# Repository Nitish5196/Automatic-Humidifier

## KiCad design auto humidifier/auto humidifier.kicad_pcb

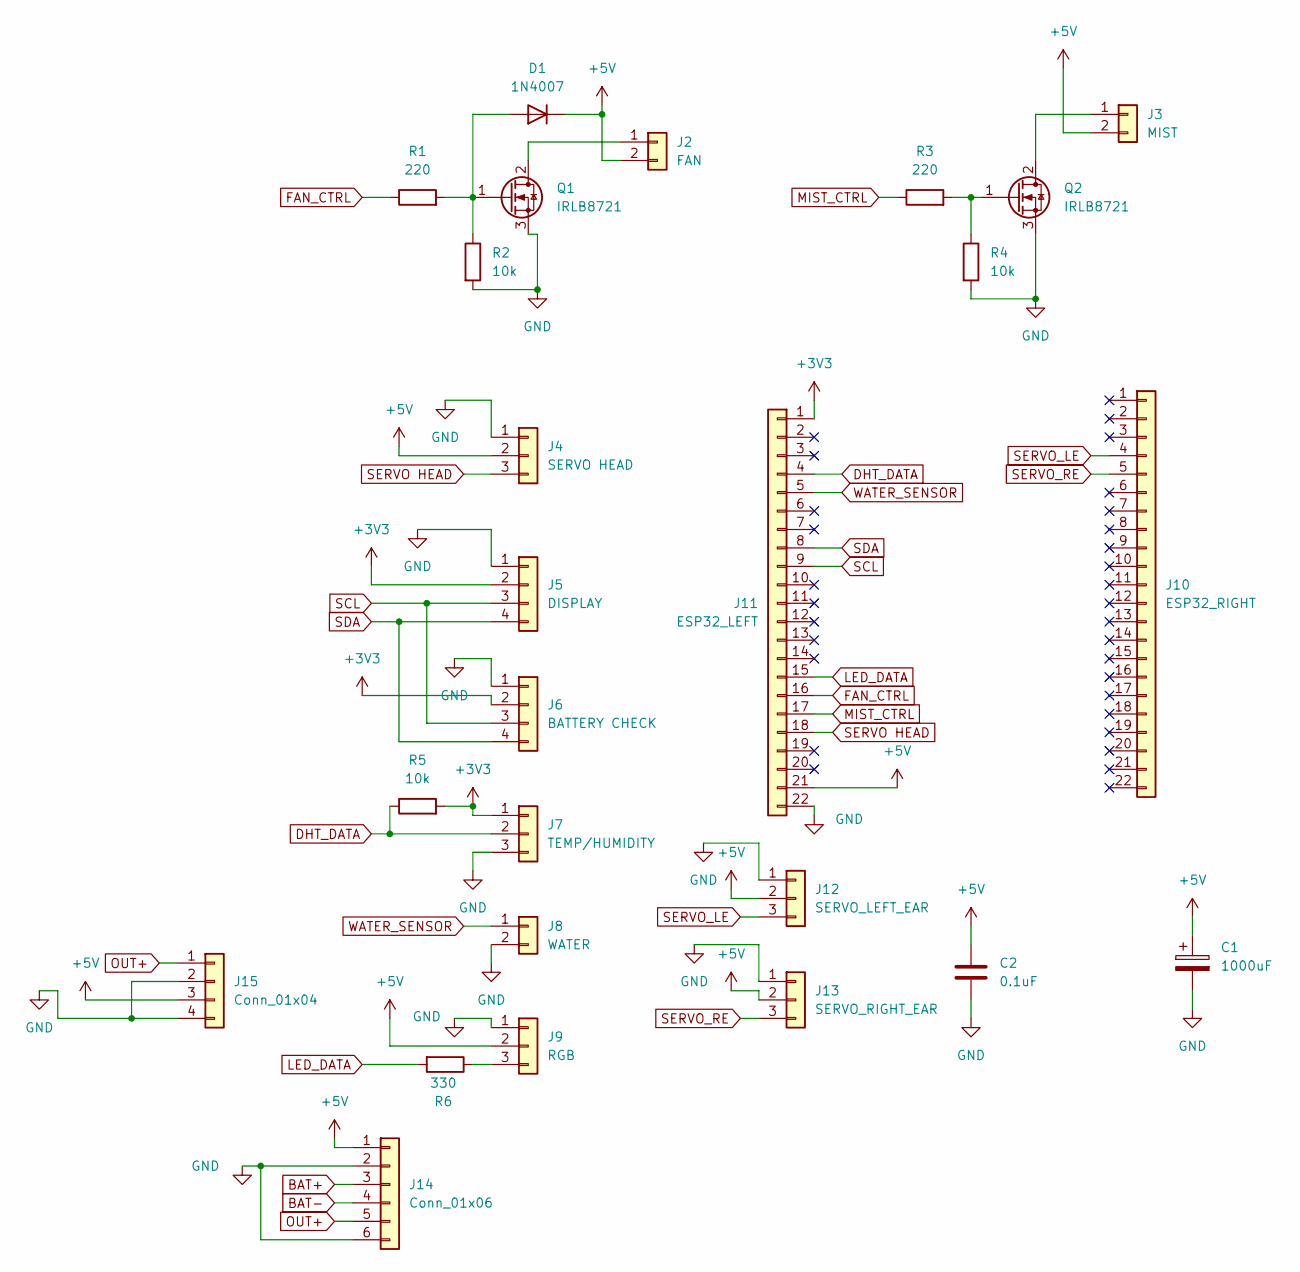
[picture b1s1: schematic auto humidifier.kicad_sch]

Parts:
C1: 1000uF; CP_Radial_D10.0mm_P5.00mm
C2: 0.1uF; C_0805_2012Metric
D1: 1N4007; D_DO-41_SOD81_P10.16mm_Horizontal
J2: FAN; PinHeader_1x02_P2.54mm_Vertical
J3: MIST; PinHeader_1x02_P2.54mm_Vertical
J4: SERVO HEAD; PinHeader_1x03_P2.54mm_Vertical
J5: DISPLAY; PinHeader_1x04_P2.54mm_Vertical
J6: BATTERY CHECK; PinHeader_1x04_P2.54mm_Vertical
J7: TEMP/HUMIDITY; PinHeader_1x03_P2.54mm_Vertical
J8: WATER; PinHeader_1x02_P2.54mm_Vertical
J9: RGB; PinHeader_1x03_P2.54mm_Vertical
J10: ESP32_RIGHT; PinSocket_1x22_P2.54mm_Vertical
J11: ESP32_LEFT; PinSocket_1x22_P2.54mm_Vertical
J12: SERVO_LEFT_EAR; PinHeader_1x03_P2.54mm_Vertical
J13: SERVO_RIGHT_EAR; PinHeader_1x03_P2.54mm_Vertical
J14: Conn_01x06; PinHeader_1x06_P2.54mm_Vertical
J15: Conn_01x04; PinHeader_1x04_P2.54mm_Vertical
Q1, Q2: IRLB8721; TO-220-3_Vertical
R1, R3: 220; R_Axial_DIN0204_L3.6mm_D1.6mm_P5.08mm_Vertical
R2, R4, R5: 10k; R_Axial_DIN0204_L3.6mm_D1.6mm_P5.08mm_Vertical
R6: 330; R_Axial_DIN0204_L3.6mm_D1.6mm_P5.08mm_Vertical

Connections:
+3V3: J5.2, J6.2, J7.1, J11.1, R5.2
+5V: C1.1, C2.1, D1.1 (K), J2.2, J3.2, J4.2, J9.2, J11.21, J12.2, J13.2, J14.1, J15.3
BAT+: J14.3
BAT-: J14.4
DHT_DATA: J7.2, J11.4, R5.1
FAN_CTRL: J11.16, R1.1
GND: C1.2, C2.2, J4.1, J5.1, J6.1, J7.3, J8.2, J9.1, J11.22, J12.1, J13.1, J14.2, J14.6, J15.2, J15.4, Q1.3 (S), Q2.3 (S), R2.2, R4.2
LED_DATA: J11.15, R6.2
MIST_CTRL: J11.17, R3.1
unnamed: D1.2 (A), Q1.1 (G), R1.2, R2.1
unnamed: J2.1, Q1.2 (D)
unnamed: J3.1, Q2.2 (D)
unnamed: J9.3, R6.1
unnamed: Q2.1 (G), R3.2, R4.1
OUT+: J14.5, J15.1
SCL: J5.3, J6.3, J11.9
SDA: J5.4, J6.4, J11.8
SERVO HEAD: J4.3, J11.18
SERVO_LE: J10.4, J12.3
SERVO_RE: J10.5, J13.3
WATER_SENSOR: J8.1, J11.5

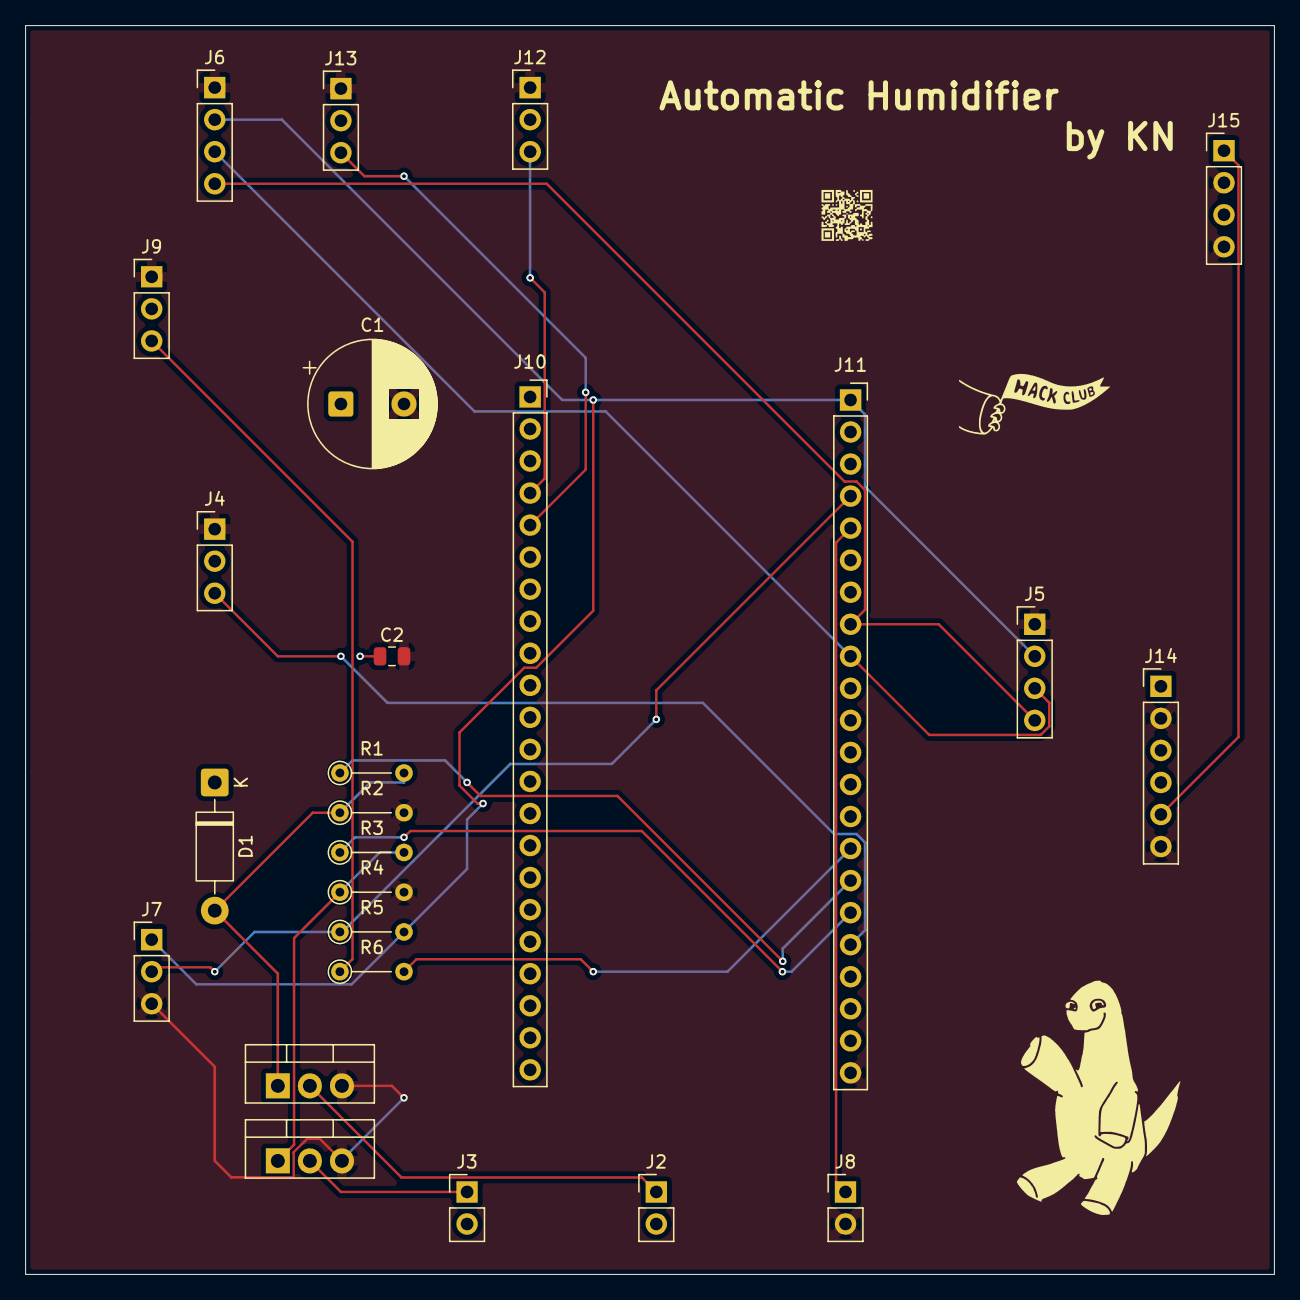
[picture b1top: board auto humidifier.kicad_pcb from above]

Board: 2 copper layers, 99.0 x 99.0 mm, 25 parts (0 on the bottom side), 19 nets.
